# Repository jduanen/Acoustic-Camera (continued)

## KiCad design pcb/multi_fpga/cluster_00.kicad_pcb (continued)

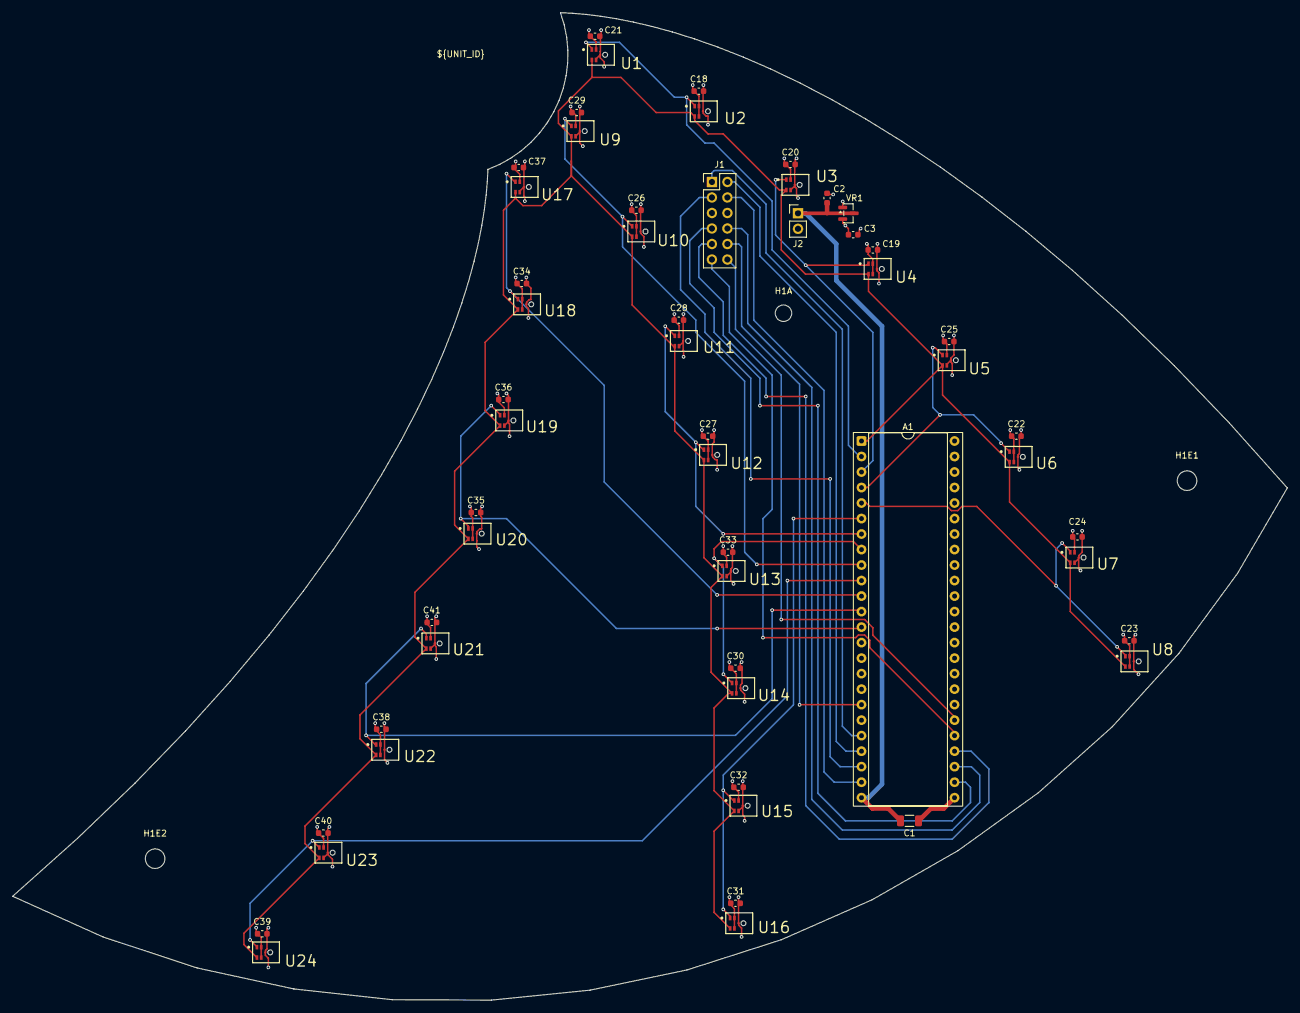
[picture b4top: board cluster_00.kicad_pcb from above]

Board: 4 copper layers, 208.8 x 161.7 mm, 58 parts (0 on the bottom side), 26 nets.

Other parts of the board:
H1A: MountingHole_2.7mm_M2.5
H1E1, H1E2: MountingHole_3.2mm_M3

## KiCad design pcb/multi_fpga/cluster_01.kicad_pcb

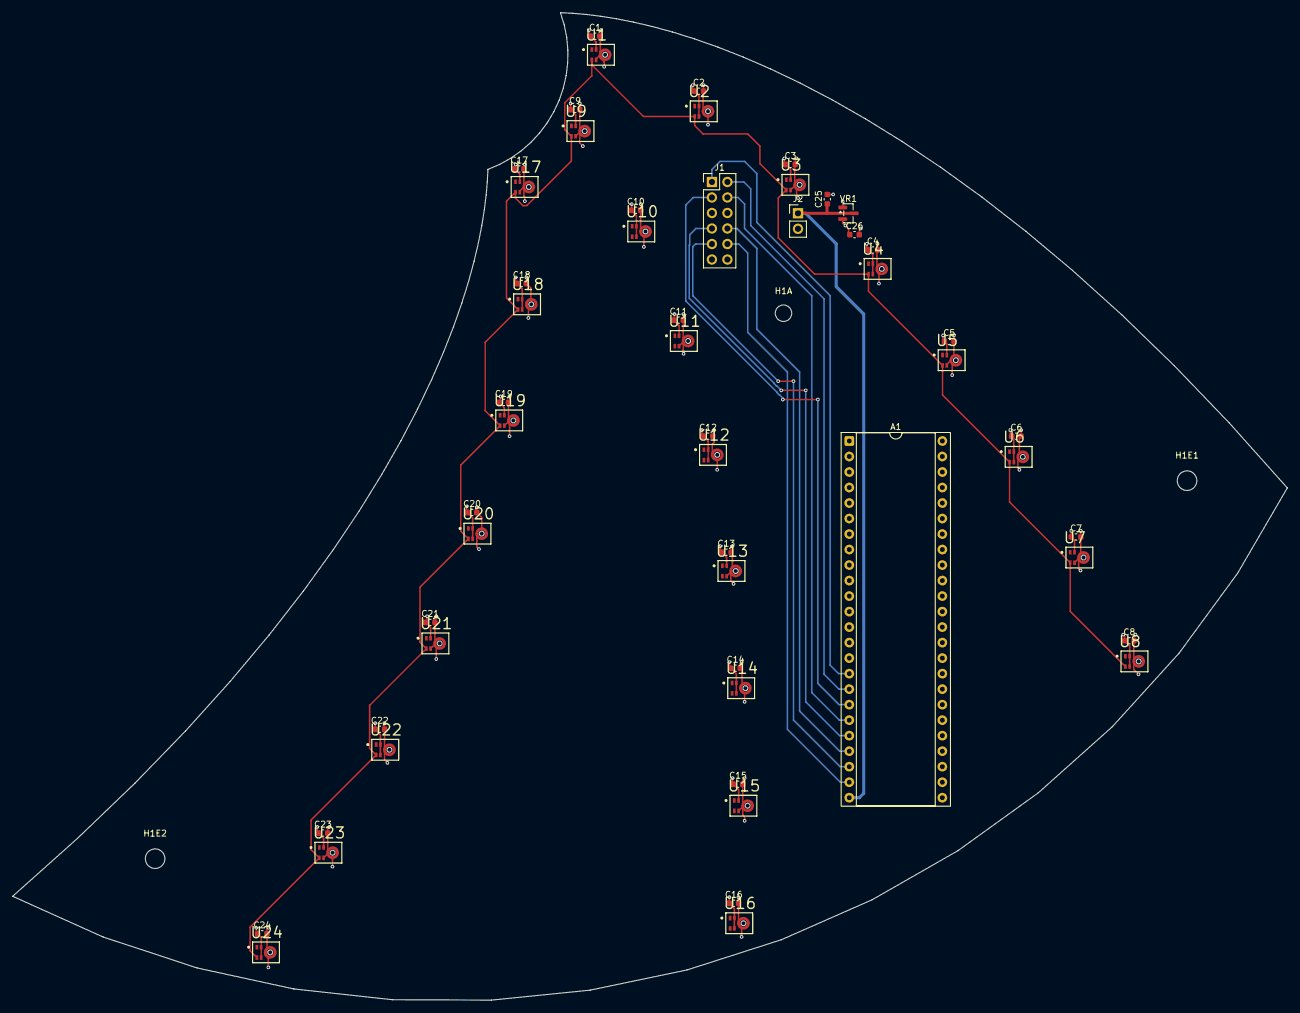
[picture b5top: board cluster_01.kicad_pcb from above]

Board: 4 copper layers, 208.8 x 161.7 mm, 57 parts (0 on the bottom side), 24 nets.

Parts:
A1: DIP-48_W15.24mm_Socket
C1, C2, C3, C4, C5, C6, C7, C8, C9, C10, C11, C12, C13, C14, C15, C16, C17, C18, C19, C20, C21, C22, C23, C24, C25, C26: C_0603_1608Metric
H1A: MountingHole_2.7mm_M2.5
H1E1, H1E2: MountingHole_3.2mm_M3
J1: PinHeader_2x06_P2.54mm_Vertical
J2: PinHeader_1x02_P2.54mm_Vertical
U1, U2, U3, U4, U5, U6, U7, U8, U9, U10, U11, U12, U13, U14, U15, U16, U17, U18, U19, U20, U21, U22, U23, U24: Comment; IFX-PG-LLGA-5-4
VR1: SOT-23

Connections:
+5V: A1.24, C25.1, J2.1, VR1.3
C0_1V8: C1.1, C2.1, C3.1, C4.1, C5.1, C6.1, C7.1, C8.1, C9.1, C10.1, C11.1, C12.1, C13.1, C14.1, C15.1, C16.1, C17.1, C18.1, C19.1, C20.1, C21.1, C22.1, C23.1, C24.1, C26.1, U1.2, U2.2, U2.4, U3.2, U4.2, U4.4, U5.2, U6.2, U6.4, U7.2, U8.2, U8.4, U9.2, U10.2, U10.4, U11.2, U12.2, U12.4, U13.2, U14.2, U14.4, U15.2, U16.2, U16.4, U17.2, U18.2, U18.4, U19.2, U20.2, U20.4, U21.2, U22.2, U22.4, U23.2, U24.2, U24.4, VR1.2
C0_PDM_CLK: A1.1, U1.3, U2.3, U3.3, U4.3, U5.3, U6.3, U7.3, U8.3, U9.3, U10.3, U11.3, U12.3, U13.3, U14.3, U15.3, U16.3, U17.3, U18.3, U19.3, U20.3, U21.3, U22.3, U23.3, U24.3
DATA_00: A1.2, U1.1, U2.1
DATA_01: A1.3, U3.1, U4.1
DATA_02: A1.4, U5.1, U6.1
DATA_03: A1.5, U7.1, U8.1
DATA_04: A1.6, U9.1, U10.1
DATA_05: A1.7, U11.1, U12.1
DATA_06: A1.8, U13.1, U14.1
DATA_07: A1.9, U15.1, U16.1
DATA_08: A1.10, U17.1, U18.1
DATA_09: A1.11, U19.1, U20.1
DATA_10: A1.12, U21.1, U22.1
DATA_11: A1.13, U23.1, U24.1
GND: A1.25, C1.2, C2.2, C3.2, C4.2, C5.2, C6.2, C7.2, C8.2, C9.2, C10.2, C11.2, C12.2, C13.2, C14.2, C15.2, C16.2, C17.2, C18.2, C19.2, C20.2, C21.2, C22.2, C23.2, C24.2, C25.2, C26.2, J2.2, U1.4, U1.5, U2.5, U3.4, U3.5, U4.5, U5.4, U5.5, U6.5, U7.4, U7.5, U8.5, U9.4, U9.5, U10.5, U11.4, U11.5, U12.5, U13.4, U13.5, U14.5, U15.4, U15.5, U16.5, U17.4, U17.5, U18.5, U19.4, U19.5, U20.5, U21.4, U21.5, U22.5, U23.4, U23.5, U24.5, VR1.1
SPOKE0_CLK: A1.23, J1.10
SPOKE0_D0: A1.16, J1.1
SPOKE0_D1: A1.17, J1.2
SPOKE0_D2: A1.18, J1.3
SPOKE0_D3: A1.19, J1.4
SPOKE0_D4: A1.20, J1.7
SPOKE0_D5: A1.21, J1.8
SPOKE0_STROBE: A1.22, J1.9

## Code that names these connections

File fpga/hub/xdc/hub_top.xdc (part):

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#
# All ports hub_top.v currently declares are populated, including the USB
# FIFO bridge (usb_framer.v -- see fpga/USB_FRAMING.md) to the FTDI UM232H
# module (A5). USB_D0-7/USB_WR_N/USB_TXE_N land on A6 DIP pins 35-44, same
# range the old (removed) async Adafruit FT232H design used -- this design
# needs one fewer pin (11 vs. 12: no RD_N/RXF_N ports, see usb_framer.v's
# header comment for why), so no spoke-bus pin needed to move.
#
# USB_CLKOUT specifically had to land on an MRCC/SRCC P-side pin (it feeds a
# BUFG in hub_top.v) -- pio[45]/U7 (IO_L19P_T3_34, where the schematic
# originally routed it) is NOT clock-capable and fails Vivado's placer with
# a hard rule_gclkio_bufg error ("Poor placement for routing between an IO
# pin and BUFG" / "IO Clock Placer failed"), confirmed by an actual
# synth+place run before the schematic was corrected -- same class of issue
# as the earlier SPOKE_CLK/PDM_D08 pin swap. Moved to pio[46]/W7
# (IO_L13P_T2_MRCC_34, P-side MRCC), which was unused and satisfies the
# requirement directly.
#
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# debugging. So PIO48/V8 is the correct FPGA-side pin regardless of jumper
# position.
#
# SPOKES_ALIVE: A6 has no PIO pins free (all 48 committed to spokes/USB/
# TCXO/reset) and its schematic symbol has no JA Pmod pins modeled. This
# signal reaches the FPGA via an external jumper cable: J18 (PMOD_Signals
# breakout, on the SpokeBus side) <-> J20 (A6_JA, DNP documentation symbol
# for the Cmod A7's on-board Pmod header) -- see hub.kicad_sch. J20 pin
# 1/2/3/4 = physical JA1/JA2/JA3/JA4 in order (confirmed with board owner).
#
# SPOKES_ALIVE is a wired-AND net now (all 4 clusters' SPOKE_ALIVE pins tied
# together on the PCB with one external pull-up, see clk_reset.v/
# reset_seq.v), collapsed from the previous 4 independent SPOKE0-3_ALIVE
# pins -- PROVISIONAL: still on JA1 (G17), the old SPOKE0_ALIVE pin, pending
# the schematic net consolidation. Re-derive from the netlist once that
# lands (JA2-4/G19,N18,L18 go free for future use in the meantime).

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set_property CFGBVS VCCO [current_design]
set_property CONFIG_VOLTAGE 3.3 [current_design]

set_property -dict { PACKAGE_PIN U8    IOSTANDARD LVCMOS33 } [get_ports { TCXO_CLK }]; #IO_L14P_T2_SRCC_34 Sch=pio[47], 12.288 MHz HCMOS TCXO (Y1)
create_clock -period 81.380 -name TCXO_CLK [get_ports { TCXO_CLK }]

set_property -dict { PACKAGE_PIN V8    IOSTANDARD LVCMOS33 } [get_ports { FPGA_RESET_N }]; #IO_L14N_T2_SRCC_34 Sch=pio[48], schematic net RESET_N (see J19 jumper note above)

set_property -dict { PACKAGE_PIN G17   IOSTANDARD LVCMOS33 } [get_ports { SPOKES_ALIVE }]; #IO_L5N_T0_D07_14 Sch=ja[1], via J18<->J20 cable -- PROVISIONAL, see note above

# SPOKE_CLK + SPOKE0-3_D0-5/STROBE: A6 DIP pins 1-14/17-23/27-34, read off
# hub.kicad_sch via `kicad-cli sch export netlist` the same way as every
# other pin above. SPOKE_CLK (pin 34) is a plain LVCMOS33 output -- not a
# clock-capable (MRCC/SRCC) pin, but that restriction only applies to clock
# *inputs* that need to reach a BUFG; this is a BUFG-sourced internal signal
# driving an ordinary output pin instead, so no placement conflict.
set_property -dict { PACKAGE_PIN M3    IOSTANDARD LVCMOS33 } [get_ports { SPOKE0_D0 }]; #IO_L8N_T1_AD14N_35 Sch=pio[01]
set_property -dict { PACKAGE_PIN L3    IOSTANDARD LVCMOS33 } [get_ports { SPOKE0_D1 }]; #IO_L8P_T1_AD14P_35 Sch=pio[02]
set_property -dict { PACKAGE_PIN A16   IOSTANDARD LVCMOS33 } [get_ports { SPOKE0_D2 }]; #IO_L12P_T1_MRCC_16 Sch=pio[03]
set_property -dict { PACKAGE_PIN K3    IOSTANDARD LVCMOS33 } [get_ports { SPOKE0_D3 }]; #IO_L7N_T1_AD6N_35 Sch=pio[04]
set_property -dict { PACKAGE_PIN C15   IOSTANDARD LVCMOS33 } [get_ports { SPOKE0_D4 }]; #IO_L11P_T1_SRCC_16 Sch=pio[05]
set_property -dict { PACKAGE_PIN H1    IOSTANDARD LVCMOS33 } [get_ports { SPOKE0_D5 }]; #IO_L3P_T0_DQS_AD5P_35 Sch=pio[06]
set_property -dict { PACKAGE_PIN A15   IOSTANDARD LVCMOS33 } [get_ports { SPOKE0_STROBE }]; #IO_L6N_T0_VREF_16 Sch=pio[07]

set_property -dict { PACKAGE_PIN B15   IOSTANDARD LVCMOS33 } [get_ports { SPOKE1_D0 }]; #IO_L11N_T1_SRCC_16 Sch=pio[08]
set_property -dict { PACKAGE_PIN A14   IOSTANDARD LVCMOS33 } [get_ports { SPOKE1_D1 }]; #IO_L6P_T0_16 Sch=pio[09]
set_property -dict { PACKAGE_PIN J3    IOSTANDARD LVCMOS33 } [get_ports { SPOKE1_D2 }]; #IO_L7P_T1_AD6P_35 Sch=pio[10]
set_property -dict { PACKAGE_PIN J1    IOSTANDARD LVCMOS33 } [get_ports { SPOKE1_D3 }]; #IO_L3N_T0_DQS_AD5N_35 Sch=pio[11]
set_property -dict { PACKAGE_PIN K2    IOSTANDARD LVCMOS33 } [get_ports { SPOKE1_D4 }]; #IO_L5P_T0_AD13P_35 Sch=pio[12]
set_property -dict { PACKAGE_PIN L1    IOSTANDARD LVCMOS33 } [get_ports { SPOKE1_D5 }]; #IO_L6N_T0_VREF_35 Sch=pio[13]
set_property -dict { PACKAGE_PIN L2    IOSTANDARD LVCMOS33 } [get_ports { SPOKE1_STROBE }]; #IO_L5N_T0_AD13N_35 Sch=pio[14]

# A6 DIP pins 15/16 (AIN15/AIN16) skipped -- dedicated XADC analog inputs,
# not usable as GPIO (confirmed, not wired to anything in hub.kicad_sch).

set_property -dict { PACKAGE_PIN M1    IOSTANDARD LVCMOS33 } [get_ports { SPOKE2_D0 }]; #IO_L9N_T1_DQS_AD7N_35 Sch=pio[17]
set_property -dict { PACKAGE_PIN N3    IOSTANDARD LVCMOS33 } [get_ports { SPOKE2_D1 }]; #IO_L12P_T1_MRCC_35 Sch=pio[18]
set_property -dict { PACKAGE_PIN P3    IOSTANDARD LVCMOS33 } [get_ports { SPOKE2_D2 }]; #IO_L12N_T1_MRCC_35 Sch=pio[19]
set_property -dict { PACKAGE_PIN M2    IOSTANDARD LVCMOS33 } [get_ports { SPOKE2_D3 }]; #IO_L9P_T1_DQS_AD7P_35 Sch=pio[20]
set_property -dict { PACKAGE_PIN N1    IOSTANDARD LVCMOS33 } [get_ports { SPOKE2_D4 }]; #IO_L10N_T1_AD15N_35 Sch=pio[21]
set_property -dict { PACKAGE_PIN N2    IOSTANDARD LVCMOS33 } [get_ports { SPOKE2_D5 }]; #IO_L10P_T1_AD15P_35 Sch=pio[22]
set_property -dict { PACKAGE_PIN P1    IOSTANDARD LVCMOS33 } [get_ports { SPOKE2_STROBE }]; #IO_L19N_T3_VREF_35 Sch=pio[23]

# A6 DIP pins 24/25 (+5V/GND) skipped -- power, not signal.

set_property -dict { PACKAGE_PIN T3    IOSTANDARD LVCMOS33 } [get_ports { SPOKE3_D0 }]; #IO_L2N_T0_34 Sch=pio[27]
set_property -dict { PACKAGE_PIN R2    IOSTANDARD LVCMOS33 } [get_ports { SPOKE3_D1 }]; #IO_L1P_T0_34 Sch=pio[28]
set_property -dict { PACKAGE_PIN T1    IOSTANDARD LVCMOS33 } [get_ports { SPOKE3_D2 }]; #IO_L3P_T0_DQS_34 Sch=pio[29]
set_property -dict { PACKAGE_PIN T2    IOSTANDARD LVCMOS33 } [get_ports { SPOKE3_D3 }]; #IO_L1N_T0_34 Sch=pio[30]
set_property -dict { PACKAGE_PIN U1    IOSTANDARD LVCMOS33 } [get_ports { SPOKE3_D4 }]; #IO_L3N_T0_DQS_34 Sch=pio[31]
set_property -dict { PACKAGE_PIN W2    IOSTANDARD LVCMOS33 } [get_ports { SPOKE3_D5 }]; #IO_L5N_T0_34 Sch=pio[32]
set_property -dict { PACKAGE_PIN V2    IOSTANDARD LVCMOS33 } [get_ports { SPOKE3_STROBE }]; #IO_L5P_T0_34 Sch=pio[33]

set_property -dict { PACKAGE_PIN W3    IOSTANDARD LVCMOS33 } [get_ports { SPOKE_CLK }]; #IO_L6N_T0_VREF_34 Sch=pio[34], shared by all 4 SpokeBus connectors on the PCB (see hub_top.v)
# Generated clock defined on bufg_sclk's output pin (the net that actually
# clocks the 4 spoke_deframer instances internally), not the SPOKE_CLK port
# itself -- the port is a separate OBUF fanout of the same sclk_r register,
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}]

# USB FIFO bridge (A5, FTDI UM232H) -- see USB_FRAMING.md. Net -> DIP pin
# read off hub.kicad_sch the same way as every pin above; USB_CLKOUT's pin
# choice is explained in this file's header comment.
set_property -dict { PACKAGE_PIN W7    IOSTANDARD LVCMOS33 } [get_ports { USB_CLKOUT }]; #IO_L13P_T2_MRCC_34 Sch=pio[46]
set_property -dict { PACKAGE_PIN V3    IOSTANDARD LVCMOS33 } [get_ports { USB_D0 }]; #IO_L6P_T0_34 Sch=pio[35]
set_property -dict { PACKAGE_PIN W5    IOSTANDARD LVCMOS33 } [get_ports { USB_D1 }]; #IO_L12P_T1_MRCC_34 Sch=pio[36]
set_property -dict { PACKAGE_PIN V4    IOSTANDARD LVCMOS33 } [get_ports { USB_D2 }]; #IO_L11N_T1_SRCC_34 Sch=pio[37]
set_property -dict { PACKAGE_PIN U4    IOSTANDARD LVCMOS33 } [get_ports { USB_D3 }]; #IO_L11P_T1_SRCC_34 Sch=pio[38]
set_property -dict { PACKAGE_PIN V5    IOSTANDARD LVCMOS33 } [get_ports { USB_D4 }]; #IO_L16N_T2_34 Sch=pio[39]
set_property -dict { PACKAGE_PIN W4    IOSTANDARD LVCMOS33 } [get_ports { USB_D5 }]; #IO_L12N_T1_MRCC_34 Sch=pio[40]
set_property -dict { PACKAGE_PIN U5    IOSTANDARD LVCMOS33 } [get_ports { USB_D6 }]; #IO_L16P_T2_34 Sch=pio[41]
set_property -dict { PACKAGE_PIN U2    IOSTANDARD LVCMOS33 } [get_ports { USB_D7 }]; #IO_L9N_T1_DQS_34 Sch=pio[42]
set_property -dict { PACKAGE_PIN W6    IOSTANDARD LVCMOS33 } [get_ports { USB_WR_N }]; #IO_L13N_T2_MRCC_34 Sch=pio[43]
set_property -dict { PACKAGE_PIN U3    IOSTANDARD LVCMOS33 } [get_ports { USB_TXE_N }]; #IO_L9P_T1_DQS_34 Sch=pio[44]

# USB_CLKOUT: a real, independent clock (FT232H's own 60MHz oscillator, not
# derived from TCXO_CLK) -- create_clock, not a generated clock.
create_clock -period 16.667 -name usb_clk_pin [get_ports { USB_CLKOUT }]

# usb_clk has no fixed phase relationship to clk/sclk (genuinely
# asynchronous, unlike sclk which is generated from clk) -- first
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# USB_D0-7/USB_WR_N/USB_TXE_N: same reasoning as SPOKE_CLK/SPOKE_D* above --
# genuinely untimed by design (no real board-trace numbers to constrain
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
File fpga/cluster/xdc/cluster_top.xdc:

# Cluster FPGA (Digilent Cmod A7-35T, part xc7a35tcpg236-1) pin constraints
# for cluster_top.v.
#
# The cluster FPGA moved from the Cmod S7 (XC7S25) to the Cmod A7-35T
# (XC7A35T) -- same DIP-48 socket footprint as the S7 (see
# pcb/multi_fpga/Readme.txt/SCHEMATIC_NOTES.md), swapped because the S7
# couldn't fit this design (needed ~17,600-19,550 LUTs at place_design time
# vs 14,600 available -- opt_design's own report_utilization undersold this,
# see the LUT-crisis conversation this swap came out of). The two chips
# don't share the same clock-capable-pin layout despite sharing a socket, so
# SPOKE_CLK also moved DIP pins (see below) and PDM_D08-11 were reshuffled
# to fill in behind it -- confirmed via `kicad-cli sch export netlist`
# against pcb/multi_fpga/cluster_00.kicad_sch's current wiring, same
# cross-check method as the S7 XDC used. PIOnn -> silicon PACKAGE_PIN taken
# from fpga/demo/CmodA735tDemo/Src/CmodA735tDemo.xdc (Digilent's own master
# XDC for this module, used identically for the hub board's XDC).
#
# All 26 ports are populated.

# Bank 0 (config) voltage: the Cmod A7-35T's configuration bank runs off the
# module's own 3.3V rail, matching every IOSTANDARD LVCMOS33 used below.
set_property CFGBVS VCCO [current_design]
set_property CONFIG_VOLTAGE 3.3 [current_design]

set_property -dict { PACKAGE_PIN N3    IOSTANDARD LVCMOS33 } [get_ports { SPOKE_CLK }]; #IO_L12P_T1_MRCC_35 Sch=pio[18], schematic net SPOKE0_CLK -- clock-capable, P-side (MRCC)
create_clock -period 162.760 -name SPOKE_CLK [get_ports { SPOKE_CLK }]

set_property -dict { PACKAGE_PIN T1    IOSTANDARD LVCMOS33 PULLTYPE PULLUP } [get_ports { FPGA_RESET_N }]; #IO_L3P_T0_DQS_34 Sch=pio[29]
set_property -dict { PACKAGE_PIN T2    IOSTANDARD LVCMOS33 } [get_ports { SPOKE_ALIVE }]; #IO_L1N_T0_34 Sch=pio[30]

set_property -dict { PACKAGE_PIN M3    IOSTANDARD LVCMOS33 } [get_ports { PDM_CLK }]; #IO_L8N_T1_AD14N_35 Sch=pio[01], schematic net C0_PDM_CLK

set_property -dict { PACKAGE_PIN L3    IOSTANDARD LVCMOS33 } [get_ports { PDM_D00 }]; #IO_L8P_T1_AD14P_35 Sch=pio[02], schematic net DATA_00
set_property -dict { PACKAGE_PIN A16   IOSTANDARD LVCMOS33 } [get_ports { PDM_D01 }]; #IO_L12P_T1_MRCC_16 Sch=pio[03], schematic net DATA_01
set_property -dict { PACKAGE_PIN K3    IOSTANDARD LVCMOS33 } [get_ports { PDM_D02 }]; #IO_L7N_T1_AD6N_35 Sch=pio[04], schematic net DATA_02
set_property -dict { PACKAGE_PIN C15   IOSTANDARD LVCMOS33 } [get_ports { PDM_D03 }]; #IO_L11P_T1_SRCC_16 Sch=pio[05], schematic net DATA_03
set_property -dict { PACKAGE_PIN H1    IOSTANDARD LVCMOS33 } [get_ports { PDM_D04 }]; #IO_L3P_T0_DQS_AD5P_35 Sch=pio[06], schematic net DATA_04
set_property -dict { PACKAGE_PIN A15   IOSTANDARD LVCMOS33 } [get_ports { PDM_D05 }]; #IO_L6N_T0_VREF_16 Sch=pio[07], schematic net DATA_05
set_property -dict { PACKAGE_PIN B15   IOSTANDARD LVCMOS33 } [get_ports { PDM_D06 }]; #IO_L11N_T1_SRCC_16 Sch=pio[08], schematic net DATA_06
set_property -dict { PACKAGE_PIN A14   IOSTANDARD LVCMOS33 } [get_ports { PDM_D07 }]; #IO_L6P_T0_16 Sch=pio[09], schematic net DATA_07
set_property -dict { PACKAGE_PIN J3    IOSTANDARD LVCMOS33 } [get_ports { PDM_D08 }]; #IO_L7P_T1_AD6P_35 Sch=pio[10], schematic net DATA_08
set_property -dict { PACKAGE_PIN J1    IOSTANDARD LVCMOS33 } [get_ports { PDM_D09 }]; #IO_L3N_T0_DQS_AD5N_35 Sch=pio[11], schematic net DATA_09
set_property -dict { PACKAGE_PIN K2    IOSTANDARD LVCMOS33 } [get_ports { PDM_D10 }]; #IO_L5P_T0_AD13P_35 Sch=pio[12], schematic net DATA_10
set_property -dict { PACKAGE_PIN L1    IOSTANDARD LVCMOS33 } [get_ports { PDM_D11 }]; #IO_L6N_T0_VREF_35 Sch=pio[13], schematic net DATA_11

set_property -dict { PACKAGE_PIN M2    IOSTANDARD LVCMOS33 } [get_ports { SPOKE_D0 }]; #IO_L9P_T1_DQS_AD7P_35 Sch=pio[20], schematic net SPOKE0_D0
set_property -dict { PACKAGE_PIN N1    IOSTANDARD LVCMOS33 } [get_ports { SPOKE_D1 }]; #IO_L10N_T1_AD15N_35 Sch=pio[21], schematic net SPOKE0_D1
set_property -dict { PACKAGE_PIN N2    IOSTANDARD LVCMOS33 } [get_ports { SPOKE_D2 }]; #IO_L10P_T1_AD15P_35 Sch=pio[22], schematic net SPOKE0_D2
set_property -dict { PACKAGE_PIN P1    IOSTANDARD LVCMOS33 } [get_ports { SPOKE_D3 }]; #IO_L19N_T3_VREF_35 Sch=pio[23], schematic net SPOKE0_D3
set_property -dict { PACKAGE_PIN R3    IOSTANDARD LVCMOS33 } [get_ports { SPOKE_D4 }]; #IO_L2P_T0_34 Sch=pio[26], schematic net SPOKE0_D4
set_property -dict { PACKAGE_PIN T3    IOSTANDARD LVCMOS33 } [get_ports { SPOKE_D5 }]; #IO_L2N_T0_34 Sch=pio[27], schematic net SPOKE0_D5
set_property -dict { PACKAGE_PIN R2    IOSTANDARD LVCMOS33 } [get_ports { SPOKE_STROBE }]; #IO_L1P_T0_34 Sch=pio[28], schematic net SPOKE0_STROBE

# On-board RGB LED (LD0), Bank 16 -- common-anode, active-low. Pins taken
# from fpga/demo/CmodA735tDemo/Src/CmodA735tDemo.xdc (Digilent's own master
# XDC), same as fpga/hub/xdc/hub_top.xdc uses for its identical on-board LED
# -- NOT the demo XDC's separate led[0]/led[1] pins (A17/C16), which are a
# different, non-RGB LED.
set_property -dict { PACKAGE_PIN B16   IOSTANDARD LVCMOS33 } [get_ports { led0_g }];
set_property -dict { PACKAGE_PIN C17   IOSTANDARD LVCMOS33 } [get_ports { led0_r }];
set_property -dict { PACKAGE_PIN B17   IOSTANDARD LVCMOS33 } [get_ports { led0_b }];

# False paths (not just waived TIMING-18 warnings -- these are genuinely
# untimed by design, not "checked and found fine" or "ignored for now"):
#
# FPGA_RESET_N: asynchronous reset from the hub FPGA, run through
# clk_reset.v's own 2-FF synchronizer specifically because it's untimed
# relative to SPOKE_CLK -- there is no meaningful setup/hold relationship to
# constrain here.
set_false_path -from [get_ports { FPGA_RESET_N }]

# PDM_D00-11: pdm_line_sync.v was deliberately designed with a full extra
# clk cycle of capture margin (see that module's header comment) precisely
# so it doesn't depend on tight datasheet/trace-delay-driven timing closure
# -- a false path states that design intent accurately; a fabricated
# set_input_delay number (without real trace-length/mic-datasheet data to
# back it) would just be guessing.
set_false_path -from [get_ports { PDM_D00 PDM_D01 PDM_D02 PDM_D03 PDM_D04 PDM_D05 PDM_D06 PDM_D07 PDM_D08 PDM_D09 PDM_D10 PDM_D11 }]

# PDM_CLK, SPOKE_D0-5, SPOKE_STROBE, SPOKE_ALIVE: outputs to the local mics
# / hub board. Nothing on this FPGA depends on their timing being STA-
# verified, and the hub-side logic that would eventually care (spoke
# deframer) doesn't exist yet -- explicitly out of scope so far (see
# fpga/README.md). Revisit with real set_output_delay numbers once the hub
# side is designed and a real cross-board timing budget exists to constrain
# against.
set_false_path -to [get_ports { PDM_CLK SPOKE_D0 SPOKE_D1 SPOKE_D2 SPOKE_D3 SPOKE_D4 SPOKE_D5 SPOKE_STROBE SPOKE_ALIVE }]

# led0_r: driven from the registered rst signal, just the status LED, not
# timing-critical (same reasoning/precedent as hub_top.xdc's led0_r false
# path). led0_g/led0_b aren't listed -- they're pure constants (clk_reset.v's
# led_g_n/led_b_n assigns), no clocked fan-in to flag.
set_false_path -to [get_ports { led0_r }]

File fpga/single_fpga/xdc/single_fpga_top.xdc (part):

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#
# Clock scheme (pcb/SCHEMATIC_NOTES.md, "PDM Clock Distribution"): the
# 12.288 MHz TCXO (Y1) sits on the mic_array board and reaches the FPGA as
# TCXO_CLK over J1/J2 pin 41. The FPGA divides it by 4 to a 50 %-duty
# 3.072 MHz PDM_CLK and sends that back over J2/J1 pin 45 to the
# CDCLVC1112/CDCLVC1108 buffer tree that clocks all 96 mics.
#
# Both clocks are on front_end CON1 so CON2/CON4 can stay unpopulated.
# Ball numbers come from the AC7200 user manual's CON1 table, and the
# CON1 pin numbers from `kicad-cli sch export netlist` of
# pcb/single_fpga/front_end.kicad_sch:
#   TCXO_CLK  CON1 pin 21  B13_L5_P  Y13   (bank 13, VCCO 3.3V)
#   PDM_CLK   CON1 pin 25  B13_L7_P  AB11  (bank 13, VCCO 3.3V)

# Configuration bank 0 runs at 3.3V on the AC7200 (user manual, power section).
set_property CFGBVS VCCO [current_design]
set_property CONFIG_VOLTAGE 3.3 [current_design]

set_property -dict {PACKAGE_PIN Y13 IOSTANDARD LVCMOS33} [get_ports TCXO_CLK]
set_property -dict {PACKAGE_PIN AB11 IOSTANDARD LVCMOS33 DRIVE 12 SLEW SLOW} [get_ports PDM_CLK]

create_clock -period 81.380 -name TCXO_CLK [get_ports TCXO_CLK]

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# drives the gate of a 2N7002 that sinks one cathode of the common-anode LED on
# +5V: active high (1 = colour on); 100k gate pull-downs keep it off until the
# FPGA is configured. Gate load only, so minimum drive.
#   LED_R  CON1 pin 32  B13_L6_P  W14   (bank 13, VCCO 3.3V)
#   LED_G  CON1 pin 33  B13_L3_N  AB13  (bank 13, VCCO 3.3V)
#   LED_B  CON1 pin 34  B13_L6_N  Y14   (bank 13, VCCO 3.3V)
set_property -dict {PACKAGE_PIN W14  IOSTANDARD LVCMOS33 DRIVE 4 SLEW SLOW} [get_ports LED_R]
set_property -dict {PACKAGE_PIN AB13 IOSTANDARD LVCMOS33 DRIVE 4 SLEW SLOW} [get_ports LED_G]
set_property -dict {PACKAGE_PIN Y14  IOSTANDARD LVCMOS33 DRIVE 4 SLEW SLOW} [get_ports LED_B]
# Nothing samples the LED pins -- they change at human-visible rates -- so there is no
# timing requirement to meet. Exclude them from timing analysis.
set_false_path -to [get_ports {LED_R LED_G LED_B}]
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#   AUX_IO[3]  CON1 pin 23  B13_L5_N  AA14  J5 pin 6  J2 pin 47
#   AUX_IO[4]  CON1 pin 27  B13_L7_N  AB12  J5 pin 8  J2 pin 48
# single_fpga_top.v leaves them high-Z for now; PULLDOWN keeps the header pins at a
# defined level. AUX_IO[3]/[4] are the N sides of TCXO_CLK's and PDM_CLK's pairs, so
# if they're ever driven, keep the minimum drive and slow slew set here.
set_property -dict {PACKAGE_PIN AA15 IOSTANDARD LVCMOS33 DRIVE 4 SLEW SLOW PULLDOWN TRUE} [get_ports {AUX_IO[0]}]
set_property -dict {PACKAGE_PIN AB15 IOSTANDARD LVCMOS33 DRIVE 4 SLEW SLOW PULLDOWN TRUE} [get_ports {AUX_IO[1]}]
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#
# Input timing (rtl/pdm_sampler.v). Each line's bit for a channel is requested by a
# PDM_CLK edge and captured on the TCXO_CLK edge two cycles later (the edge that also
# launches the next PDM_CLK edge). Delays are from PDM_CLK at the FPGA pin, which the
# generated clock above already places after Vivado's own clock-to-out:
#   clock out to the mics: PDM_CLK net + U110 + arm buffer + MIC_CLK trace
#       buffers 2 x 0.8-2.0 ns (CDCLVC1112/1108 at 3.3 V)
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
# ---------------------------------------------------------------------------------------
# GbE: AC7200 200 MHz SYS_CLK -> MMCM -> 125 MHz RGMII clocks, the DP83867 (front_end U3)
# on CON3 RGMII and CON1 PHY_RESET_N. Pins from the AC7200 manual's CON1/CON3 tables and a
# kicad-cli netlist of pcb/single_fpga/front_end.kicad_sch (RGMII RX moved to bank 15 so
# BUFIO/BUFR from RXC reaches it -- see pcb/SCHEMATIC_NOTES.md "GbE PHY, RGMII and Y1").
# ---------------------------------------------------------------------------------------
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#   RGMII_TXD0-3  CON3.12/8/6/4  B16_L23_P/L21_P/L21_N/IO25  E21/B21/A21/F21
# All on CON3's even (west) row, south to north TXD3, TXD2, TXD1, TXD0, TXC, TX_CTL --
# U3's own pin order, so the TX bundle routes without crossings.
set_property -dict {PACKAGE_PIN D21 IOSTANDARD LVCMOS33 DRIVE 8 SLEW FAST} [get_ports RGMII_TXC]
set_property -dict {PACKAGE_PIN E22 IOSTANDARD LVCMOS33 DRIVE 8 SLEW FAST} [get_ports RGMII_TX_CTL]
set_property -dict {PACKAGE_PIN E21 IOSTANDARD LVCMOS33 DRIVE 8 SLEW FAST} [get_ports {RGMII_TXD[0]}]
set_property -dict {PACKAGE_PIN B21 IOSTANDARD LVCMOS33 DRIVE 8 SLEW FAST} [get_ports {RGMII_TXD[1]}]
set_property -dict {PACKAGE_PIN A21 IOSTANDARD LVCMOS33 DRIVE 8 SLEW FAST} [get_ports {RGMII_TXD[2]}]
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#   RGMII_RX_CTL  CON3.11  B15_L2_P   G15
#   RGMII_RXD0-3  CON3.7/5/13/17  B15_L4_N/L4_P/L2_N/L12_N  G18/G17/G16/H19
# All on CON3's odd (east) row, pins 5-17; RXC has to stay on CON3.15 (clock-capable).
set_property -dict {PACKAGE_PIN J19 IOSTANDARD LVCMOS33} [get_ports RGMII_RXC]
set_property -dict {PACKAGE_PIN G15 IOSTANDARD LVCMOS33} [get_ports RGMII_RX_CTL]
set_property -dict {PACKAGE_PIN G18 IOSTANDARD LVCMOS33} [get_ports {RGMII_RXD[0]}]
set_property -dict {PACKAGE_PIN G17 IOSTANDARD LVCMOS33} [get_ports {RGMII_RXD[1]}]
set_property -dict {PACKAGE_PIN G16 IOSTANDARD LVCMOS33} [get_ports {RGMII_RXD[2]}]
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
# PHY_RESET_N  CON1.28  B13_L2_N  AB17. Held low ~10 ms after configuration, then high;
# the board's R9 10k pull-up holds it high while the FPGA is unconfigured.
set_property -dict {PACKAGE_PIN AB17 IOSTANDARD LVCMOS33 DRIVE 4 SLEW SLOW} [get_ports PHY_RESET_N]
set_false_path -to [get_ports PHY_RESET_N]

# MDC  CON1.26  B13_L2_P  AB16;  MDIO  CON1.24  B13_L1_N  AA16 (R8 2.2k pull-up on board).
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# bit this end drives has ~325 ns of setup and hold at the PHY (it needs 10 ns); in the
# read-back the PHY drives MDIO <= 10 ns after an MDC rise and it's sampled as MDC next
# rises, ~650 ns later. Untimed by design.
set_property -dict {PACKAGE_PIN AB16 IOSTANDARD LVCMOS33 DRIVE 4 SLEW SLOW} [get_ports MDC]
set_property -dict {PACKAGE_PIN AA16 IOSTANDARD LVCMOS33 DRIVE 4 SLEW SLOW} [get_ports MDIO]
set_false_path -to [get_ports {MDC MDIO}]
set_false_path -from [get_ports MDIO]

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# DDR output: each data edge is checked against the same-edge TXC transition
# (multicycle setup 0 / hold -1), max = -skew_after = -0.5, min = +skew_before = 0.5,
# and the opposite-edge pairs are false paths.
create_generated_clock -name RGMII_TXC -source [get_pins mmcm_gtx/CLKOUT0] -multiply_by 1 [get_ports RGMII_TXC]
set_output_delay -clock RGMII_TXC -max -0.5 [get_ports {RGMII_TXD[*] RGMII_TX_CTL}]
set_output_delay -clock RGMII_TXC -min  0.5 [get_ports {RGMII_TXD[*] RGMII_TX_CTL}]
set_output_delay -clock RGMII_TXC -clock_fall -max -0.5 -add_delay [get_ports {RGMII_TXD[*] RGMII_TX_CTL}]
set_output_delay -clock RGMII_TXC -clock_fall -min  0.5 -add_delay [get_ports {RGMII_TXD[*] RGMII_TX_CTL}]
set_multicycle_path -setup 0 -from [get_clocks -of_objects [get_pins mmcm_gtx/CLKOUT0]] -to [get_clocks RGMII_TXC]
set_multicycle_path -hold -1 -from [get_clocks -of_objects [get_pins mmcm_gtx/CLKOUT0]] -to [get_clocks RGMII_TXC]
set_false_path -setup -rise_from [get_clocks -of_objects [get_pins mmcm_gtx/CLKOUT0]] -fall_to [get_clocks RGMII_TXC]
set_false_path -setup -fall_from [get_clocks -of_objects [get_pins mmcm_gtx/CLKOUT0]] -rise_to [get_clocks RGMII_TXC]
set_false_path -hold  -rise_from [get_clocks -of_objects [get_pins mmcm_gtx/CLKOUT0]] -fall_to [get_clocks RGMII_TXC]
set_false_path -hold  -fall_from [get_clocks -of_objects [get_pins mmcm_gtx/CLKOUT0]] -rise_to [get_clocks RGMII_TXC]

# The three clock sources are independent oscillators. Every crossing between them is
# handled in logic: the packetizer's toggle-synchronized ping-pong handoff (TCXO ->
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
